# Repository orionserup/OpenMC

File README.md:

# OpenMC

OpenMC is an Open Source motor controller which serves as an interface between digital inputs and a motor driver interface

OpenMC is designed to be an affordable, flexible, scalable, and open solution to controller small scale electric vehicles (eBikes, Electric Scooters, eSk8, etc).

OpenMC is inspired by projects like [VESC](https://vesc-project.com/)

## Authors

[Orion Serup](mailto:oserup@proton.me)

## License

OpenMC is licensed under the [Creative Commons Share-Alike License](https://creativecommons.org/licenses/by-sa/4.0/)

All derivatives of this work must contain attribution to the original author as well as the same or similar license

This project can be used in any application without restriction (including commercial) provided that proper attribution and licensing terms are met

## Getting Started

Manufacturing files and compiled documentation can be directly downloaded through the releases tab by version.

If you want to modify the source or compile the documentation you will need the following dependencies

### Dependencies

OpenMC is designed using [KiCad](https://kicad.org) Version 8

The documentation is generated using [Typst](https://typst.app)

Version control and configuration management is done by Git and hosted on GitHub

### Downloading the Repository

The files can be downloaded from git, using the Github CLI, Github Desktop (or other visual Git tool) or directly from Github

[Repository Link](https://github.com/orionserup/OpenMC)

Download the repository by going to the GitHub and click on the Code button and select a method of download

## Building the Board

If you downloaded the source files you will have to generate manufacturing files of your own if you would like to build the board based on your local version. Reference KiCad manufacturing file export guides online for the process

Otherwise the generated manufacturing files can be used to build and assemble the board at just about any PCBA manufacturer

### Manufacturing the PCB

Submit the Gerber Files with drill files in zip form (Gerbers.zip if getting from releases) to your manufacturer of choice ([JLCPCB](https://jlcpcb.com) or [PCBWay](https://pcbway.com) is recommended)

The build parameters that are recommended are as follows, these settings will most likely yield the cheapest board with the fastest turn around time

- 1.6mm PCB Height (Not important but 1.6mm is standard)
- 2 Layer PCB
- 1 oz/ft^2 Copper Thickness (Can go down to .5 Oz/ft^2)
- HASL Surface Finish (Lead Free if you want but Leaded is fine)
- Green PCB Color (Official Build use Black but Green is Cheaper and Faster)
- White Silkscreen
- Tented Vias (Untented is also fine)
- No gold fingers, castellated holes, or edge plating

Any other parameters are likely not important and can be ignored

### Sourcing Parts

It is usually possible to have the PCB manufacturer source and purchase parts which are then assembled by them, we recommend doing this if you do not have the proper equipment to solder SMD components. Inquire with your manufacturer of choice to do this

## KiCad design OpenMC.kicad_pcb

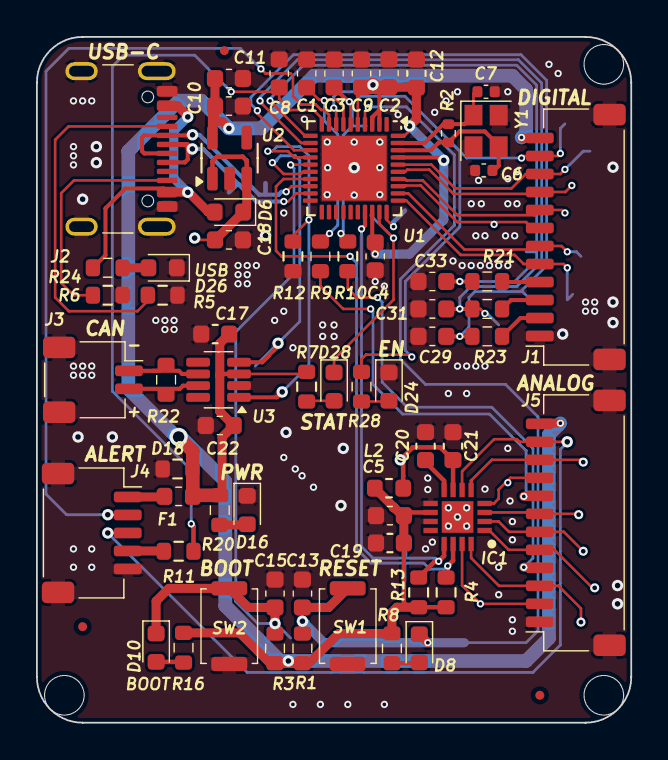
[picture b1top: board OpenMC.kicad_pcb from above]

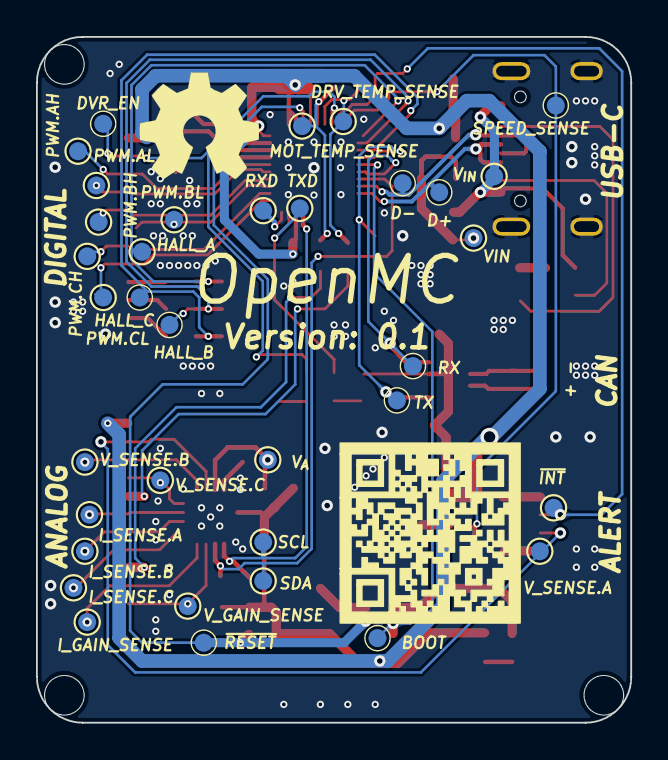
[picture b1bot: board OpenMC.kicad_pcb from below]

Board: 2 copper layers, 33.0 x 38.1 mm, 108 parts (39 on the bottom side), 57 nets.

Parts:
C1, C3, C5, C11, C13, C15, C19, C29, C31, C33: 100nF; C_0603_1608Metric
C2, C4, C8, C9, C10, C12, C17, C18, C21, C22: 4.7uF; C_0603_1608Metric
C6, C7: 10pF; C_0402_1005Metric
C20: 1uF; C_0603_1608Metric
D6: 430mV; D_0603_1608Metric
D8, D10, D16, D24: Red; LED_0603_1608Metric
D18: 10V; R_0603_1608Metric
D26, D28: Blue; LED_0603_1608Metric
F1: 1A; Fuse_0603_1608Metric
FID1, FID2, FID3: Fiducial; Fiducial_0.5mm_Mask1mm
H1, H2, H3: MountingHole; MountingHole_2.2mm_M2
IC1: TLA2528IRTER; QFN50P300X300X80-17N-D
J1: Motor Digital; JST_SH_SM12B-SRSS-TB_1x12-1MP_P1.00mm_Horizontal
J2: USB-C; USB_C_Receptacle_GCT_USB4105-xx-A_16P_TopMnt_Horizontal
J3: CAN; JST_SH_SM02B-SRSS-TB_1x02-1MP_P1.00mm_Horizontal
J4: Controller; JST_SH_SM05B-SRSS-TB_1x05-1MP_P1.00mm_Horizontal
J5: Motor Analog; JST_SH_SM12B-SRSS-TB_1x12-1MP_P1.00mm_Horizontal
L2: 1uH; L_0603_1608Metric
R1, R3, R7, R8, R9, R10, R11, R12, R16, R20, R24, R28: 4.7k; R_0603_1608Metric
R2: 1M; R_0402_1005Metric
R4, R13: 2.2k; R_0603_1608Metric
R5, R6: 5.1k; R_0603_1608Metric
R19, R21, R23: 10; R_0603_1608Metric
R22: 120; R_0603_1608Metric
SW1: RESET; SW_Push_SPST_NO_Alps_SKRK
SW2: BOOT; SW_Push_SPST_NO_Alps_SKRK
SYM1: Logo_Open_Hardware_Small; OSHW-Symbol_6.7x6mm_SilkScreen
TP1: MOT_TEMP_SENSE; TestPoint_Pad_D1.0mm
TP2: HALL_A; TestPoint_Pad_D1.0mm
TP3: HALL_B; TestPoint_Pad_D1.0mm
TP4: HALL_C; TestPoint_Pad_D1.0mm
TP5: PWM.CL; TestPoint_Pad_D1.0mm
TP6: PWM.CH; TestPoint_Pad_D1.0mm
TP7: DRV_TEMP_SENSE; TestPoint_Pad_D1.0mm
TP8: SPEED_SENSE; TestPoint_Pad_D1.0mm
TP9: PWM.BL; TestPoint_Pad_D1.0mm
TP10: PWM.BH; TestPoint_Pad_D1.0mm
TP11: PWM.AL; TestPoint_Pad_D1.0mm
TP12: PWM.AH; TestPoint_Pad_D1.0mm
TP13: SDA; TestPoint_Pad_D1.0mm
TP14: SCL; TestPoint_Pad_D1.0mm
TP15: VIN; TestPoint_Pad_D1.0mm
TP16: V_{IN}; TestPoint_Pad_D1.0mm
TP17: I_SENSE.C; TestPoint_Pad_D1.0mm
TP18: I_SENSE.B; TestPoint_Pad_D1.0mm
TP19: I_SENSE.A; TestPoint_Pad_D1.0mm
TP20: V_SENSE.C; TestPoint_Pad_D1.0mm
TP21: DVR_EN; TestPoint_Pad_D1.0mm
TP22: BOOT; TestPoint_Pad_D1.0mm
TP23: D+; TestPoint_Pad_D1.0mm
TP24: D-; TestPoint_Pad_D1.0mm
TP25: ~{RESET}; TestPoint_Pad_D1.0mm
TP26: TXD; TestPoint_Pad_D1.0mm
TP27: RXD; TestPoint_Pad_D1.0mm
TP28: RX; TestPoint_Pad_D1.0mm
TP29: TX; TestPoint_Pad_D1.0mm
TP30: V_SENSE.B; TestPoint_Pad_D1.0mm
TP31: V_SENSE.A; TestPoint_Pad_D1.0mm
TP32: V_{A}; TestPoint_Pad_D1.0mm
TP33: V_GAIN_SENSE; TestPoint_Pad_D1.0mm
TP34: I_GAIN_SENSE; TestPoint_Pad_D1.0mm
TP35: ~{INT}; TestPoint_Pad_D1.0mm
U1: ESP32-C6; QFN-40-1EP_5x5mm_P0.4mm_EP3.6x3.6mm
U2: AP2204K-3.3; SOT-23-5
U3: TCAN334; SOT-23-8
Y1: 40MHz; Crystal_SMD_2520-4Pin_2.5x2.0mm

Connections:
/3 Volt Supply/VIN: C18.1, D6.1 (K), TP15.1, U2.1 (VIN), U2.3 (EN)
/ADC/V_{A}: C21.1, IC1.7 (AVDD), L2.2, TP32.1
/AH: J1.10, TP12.1, U1.36 (GPIO23/SDIO_DATA3)
/AL: J1.9, TP11.1, U1.35 (GPIO22/SDIO_DATA2)
/BH: J1.8, TP10.1, U1.34 (GPIO21/SDIO_DATA1/FSPICS5)
/BL: J1.7, TP9.1, U1.33 (GPIO20/SDIO_DATA0/FSPICS4)
/CAN+: J3.2, R22.1, U3.7 (CANH)
/CAN-: J3.1, R22.2, U3.6 (CANL)
/CH: J1.6, TP6.1, U1.32 (GPIO19/SDIO_CLK/FSPICS3)
/CL: J1.5, TP5.1, U1.31 (GPIO18/SDIO_CMD/FSPICS2)
/D+: J2.A6 (D+), J2.B6 (D+), TP23.1, U1.19 (GPIO13/USB_D+)
/D-: J2.A7 (D-), J2.B7 (D-), TP24.1, U1.18 (GPIO12/USB_D-)
/DRIVER_TEMP_SENSE: J5.8, R9.2
/DRV_EN: J1.11, R28.1, TP21.1, U1.8 (GPIO2/FSPIQ/ADC1_CH2)
/GND: C1.2, C2.2, C3.2, C4.2, C5.2, C6.1, C7.1, C8.2, C9.2, C10.2, C11.2, C12.2, C13.2, C15.2, C17.2, C18.2, C19.2, C20.2, C21.2, C22.2, C29.2, C31.2, C33.2, D16.1 (K), D18.1 (A1), D24.1 (K), D26.1 (K), IC1.9 (GND), IC1.11 (ADDR), IC1.17 (EP), J1.1, J1.MP (MountPin), J2.A1 (GND), J2.A12 (GND), J2.B1 (GND), J2.B12 (GND), J2.S1 (SHIELD), J3.MP (MountPin), J4.5, J4.MP (MountPin), J5.1, J5.MP (MountPin), R5.1, R6.1, R12.2, SW1.1 (A), SW2.1 (A), U1.41 (GND), U2.2 (GND), U3.2 (GND), Y1.2, Y1.4
/HALL.A: J1.4, R19.1
/HALL.B: J1.3, R21.1
/HALL.C: J1.2, R23.1
/IGAIN_SENSE: IC1.16 (AIN1/GPIO1), J5.3, TP34.1
/I_SENSE.A: IC1.3 (AIN4/GPIO4), J5.7, TP19.1
/I_SENSE.B: IC1.2 (AIN3/GPIO3), J5.6, TP18.1
/I_SENSE.C: IC1.1 (AIN2/GPIO2), J5.5, TP17.1
/MOTOR_TEMP_SENSE: J5.4, R10.2
/Motor Controller /BOOT: C15.1, D10.1 (K), R3.1, SW2.2 (B), TP22.1, U1.15 (GPIO9)
/Motor Controller /DRV_TEMP_SENSE: C1.1, R9.1, TP7.1, U1.7 (GPIO1/XTAL_32K_N/ADC1_CH1)
/Motor Controller /HALL_A: C33.1, R19.2, TP2.1, U1.11 (MTDI/GPIO5/FSPIWP/ADC1_CH5)
/Motor Controller /HALL_B: C31.1, R21.2, TP3.1, U1.12 (MTCK/GPIO6/FSPICLK/ADC1_CH6)
/Motor Controller /HALL_C: C29.1, R23.2, TP4.1, U1.13 (MTDO/GPIO7/FSPID)
/Motor Controller /MOT_TEMP_SENSE: C3.1, R10.1, TP1.1, U1.6 (GPIO0/XTAL_32K_P/ADC1_CH0)
/Motor Controller /RXD: TP27.1, U1.30 (U0RXD/GPIO17/FSPICS1)
/Motor Controller /SPEED_SENSE: C8.1, R11.1, TP8.1, U1.10 (MTMS/GPIO4/FSPIHD/ADC1_CH4)
/Motor Controller /TXD: D28.1 (K), TP26.1, U1.29 (U0TXD/GPIO16/FSPICS0)
/Motor Controller /V_{DD}: C2.1, C4.1, C5.1, C9.1, C10.1, C11.1, C12.1, C17.1, C19.1, C22.1, D18.2 (A2), F1.1, IC1.10 (DVDD), J1.12, J5.12, L2.1, R1.2, R3.2, R4.2, R7.2, R8.2, R13.2, R16.2, R20.1, U1.2 (VDDA3P3), U1.3 (VDDA3P3), U1.5 (VDDPST1), U1.28 (VDDPST2), U1.37 (VDDA1), U1.40 (VDDA2), U2.5 (VOUT), U3.3 (VCC)
/Motor Controller /X+: C7.2, R2.1, U1.39 (XTAL_P), Y1.1
/Motor Controller /X-: C6.2, R2.2, U1.38 (XTAL_N), Y1.3
/Motor Controller /~RESET: C13.1, D8.1 (K), R1.1, SW1.2 (B), TP25.1, U1.4 (CHIP_PU)
/RX: TP28.1, U1.16 (GPIO10), U3.4 (RXD)
/SCL: IC1.13 (SCL), R13.1, TP14.1, U1.27 (GPIO15)
/SDA: IC1.14 (SDA), R4.1, TP13.1, U1.17 (GPIO11)
/SPEED_CTRL_SENSE: J4.4, R11.2
/TX: R12.1, TP29.1, U1.14 (GPIO8), U3.1 (TXD)
/VGAIN_SENSE: IC1.15 (AIN0/GPIO0), J5.2, TP33.1
/V_SENSE.A: IC1.6 (AIN7/GPIO7), J4.3, J5.11, TP31.1
/V_SENSE.B: IC1.5 (AIN6/GPIO6), J5.10, TP30.1
/V_SENSE.C: IC1.4 (AIN5/GPIO5), J5.9, TP20.1
/V_{BUS}: D6.2 (A), J2.A4 (VBUS), J2.A9 (VBUS), J2.B4 (VBUS), J2.B9 (VBUS), R24.1, TP16.1
/~INT: J4.2, TP35.1, U1.9 (GPIO3/ADC1_CH3)
unnamed: D8.2 (A), R8.1
unnamed: D10.2 (A), R16.1
unnamed: D16.2 (A), R20.2
unnamed: D24.2 (A), R28.2
unnamed: D26.2 (A), R24.2
unnamed: D28.2 (A), R7.1
unnamed: C20.1, IC1.8 (DECAP)
unnamed: J2.A5 (CC1), R5.2
unnamed: J2.B5 (CC2), R6.2
unnamed: F1.2, J4.1

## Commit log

2024-04-07 first initial version
2024-04-11 updated to external adc
2024-04-13 hello

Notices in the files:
OpenMC.kicad_pcb:
License: CC BY-SA
